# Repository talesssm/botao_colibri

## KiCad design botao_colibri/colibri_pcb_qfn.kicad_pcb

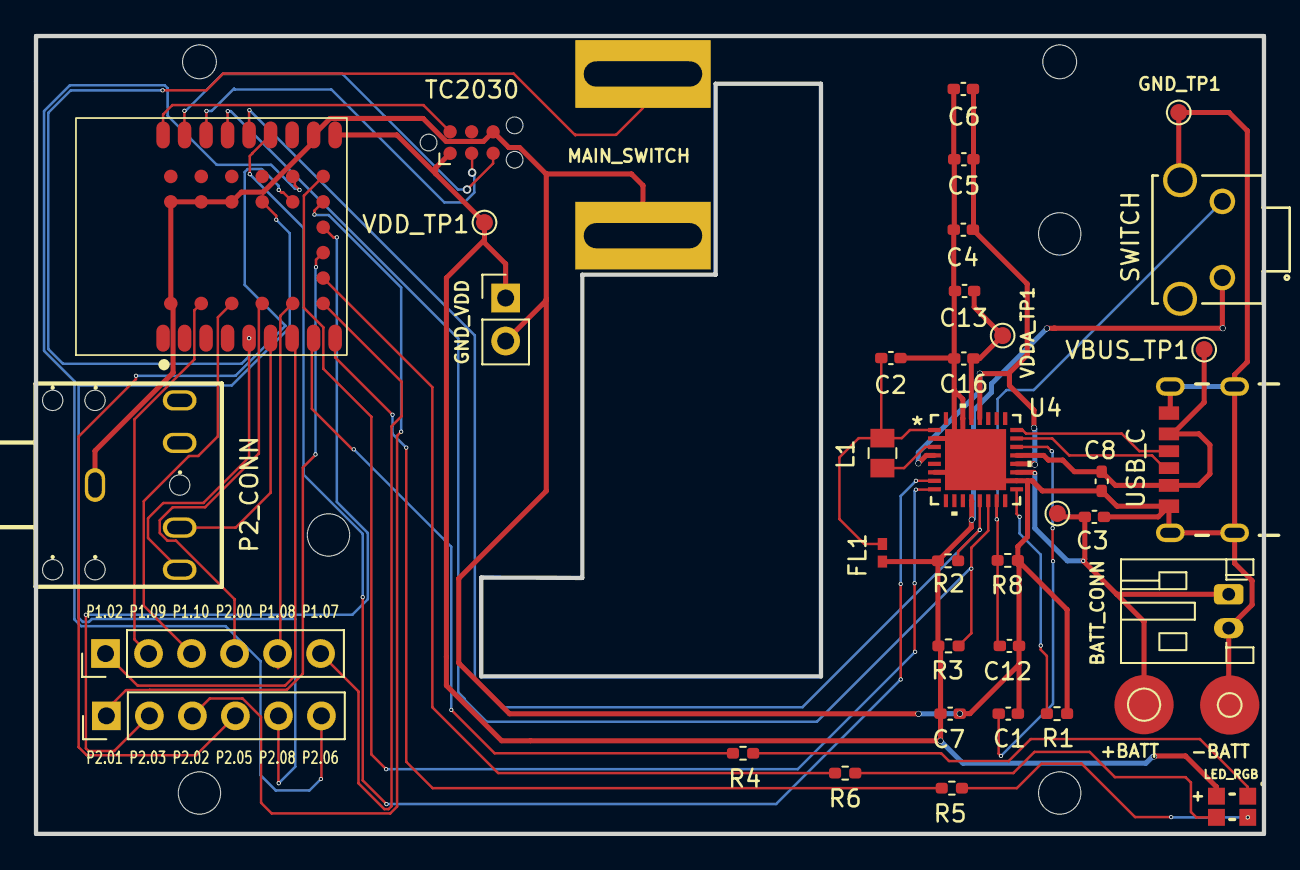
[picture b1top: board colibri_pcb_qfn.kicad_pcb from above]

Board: 2 copper layers, 72.5 x 47.1 mm, 45 parts (0 on the bottom side), 40 nets.

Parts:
+BATT: Conn_01x02; TestPoint_Pad_D1.5mm
-BATT: TestPoint; TestPoint_Pad_D1.0mm
BATT_CONN: Conn_01x02; JST_PH_S2B-PH-K_1x02_P2.00mm_Horizontal
C1, C3, C4, C5, C6, C7, C8: C_Small; C_0402_1005Metric_Pad0.74x0.62mm_HandSolder
C2: 10µF; C_0402_1005Metric_Pad0.74x0.62mm_HandSolder
C12, C13: 100nF; C_0402_1005Metric_Pad0.74x0.62mm_HandSolder
C16: 1uF; C_0402_1005Metric_Pad0.74x0.62mm_HandSolder
FL1: BLM15AG121SN1D; IND_BLM15_0402_MUR
GND_TP1: TestPoint; TestPoint_Pad_D1.0mm
GND_VDD: Conn_01x02; PinHeader_1x02_P2.54mm_Vertical
H1, H2, H3, H4, H5, H6: NPTH
L1: 2.2µH; LQM21PN2R2MGRD
LED_RGB: WL-SFCD_0805
MAIN_SWITCH: SW_Push; sw_principal
P1.02 P1.09 P1.10 P2.00 P1.08 P1.07, P2.01 P2.03 P2.02 P2.05 P2.08 P2.06: Conn_01x06; PinHeader_1x06_P2.54mm_Vertical
P2_CONN: PJ-307C; AUDIO-TH_PJ307C
R1: 360kR; R_0402_1005Metric_Pad0.72x0.64mm_HandSolder
R2, R3: 4.7kR; R_0402_1005Metric_Pad0.72x0.64mm_HandSolder
R4, R5, R6: R_Small; R_0402_1005Metric_Pad0.72x0.64mm_HandSolder
R8: 330kR; R_0402_1005Metric_Pad0.72x0.64mm_HandSolder
SWITCH: B3F-3122
TC2030: TC2030; Tag-Connect_TC2030-IDC-NL_2x03_P1.27mm_Vertical
U1: ME54BS12; ME54BS12_V1.0
U4: NPM1300-QEAA-R7; NPM1300_QFN32_5X5_NOR
USB_C: USB4970-00-A_REVA; GCT_USB4970-00-A_REVA
VBATT_TP1: TestPoint; TestPoint_Pad_D1.0mm
VBUS_TP1: TestPoint; TestPoint_Pad_D1.0mm
VDDA_TP1: TestPoint; TestPoint_Pad_D1.0mm
VDD_TP1: TestPoint; TestPoint_Pad_D1.0mm

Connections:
+BATT: +BATT.1 (Pin_1_1), BATT_CONN.1, C3.1, U4.19 (VBAT), VBATT_TP1.1 (1_1)
BTN_PWR: C12.1, R8.2, SWITCH.2, U4.15 (SHPHLD)
GND: -BATT.1 (1_1), BATT_CONN.2, C1.2, C2.2, C3.2, C4.2, C5.2, C6.2, C7.2, C8.2, C12.2, C13.2, C16.2, GND_TP1.1 (1_1), GND_VDD.2, MAIN_SWITCH.2, P2_CONN.1, R1.1, R8.1, SWITCH.4, TC2030.6, U1.11 (GND), U1.A1 (GND), U1.A5 (GND), U1.B5 (GND), U1.C5 (GND), U4.2 (PVSS1), U4.6 (PVSS2), U4.18 (NTC), U4.30 (LSIN2/VINLDO2), U4.31 (LSOUT2/VOUTLDO2), U4.33 (AVSS), USB_C.A12 (GND), USB_C.B12 (GND), USB_C.SH1 (SHELL_GND), USB_C.SH2 (SHELL_GND), USB_C.SH3 (SHELL_GND), USB_C.SH4 (SHELL_GND)
I2C_SCL: R3.1, U1.15 (P0.03), U4.14 (SCL)
I2C_SDA: R2.1, U1.14 (P0.02), U4.13 (SDA)
LED_B: R6.2, U1.F2 (P1.04/AIN0)
LED_G: R5.2, U1.9 (P1.05/AIN1)
LED_R: R4.1, U1.8 (P1.06/AIN2)
NPM1300_EN: U1.F6 (P2.04), U4.8 (GPIO1)
NPM1300_INT: U1.13 (P0.01), U4.7 (GPIO0)
NRESET: TC2030.2, U1.18 (~NRESET)
unnamed: LED_RGB.1, R4.2
unnamed: LED_RGB.2, R5.1
unnamed: LED_RGB.3, R6.1
unnamed: L1.2, U4.3 (SW1)
unnamed: C1.1, U4.22 (VBUSOUT)
unnamed: C2.1, FL1.1, L1.1, U4.1 (VOUT1)
unnamed: R1.2, U4.17 (VSET1)
P1.02: P1.02 P1.09 P1.10 P2.00 P1.08 P1.07.1, U1.7 (P1.02/NFC1)
P1.07: P1.02 P1.09 P1.10 P2.00 P1.08 P1.07.6, U1.F1 (P1.07/AIN3)
P1.08: P1.02 P1.09 P1.10 P2.00 P1.08 P1.07.5, U1.E1 (P1.08)
P1.09: P1.02 P1.09 P1.10 P2.00 P1.08 P1.07.2, U1.B1 (P1.09)
P1.10: P1.02 P1.09 P1.10 P2.00 P1.08 P1.07.3, U1.C1 (P1.10)
P2.00: P1.02 P1.09 P1.10 P2.00 P1.08 P1.07.4, U1.D1 (P2.00)
P2.01: P2.01 P2.03 P2.02 P2.05 P2.08 P2.06.1, U1.F3 (P2.01)
P2.02: P2.01 P2.03 P2.02 P2.05 P2.08 P2.06.3, U1.F5 (P2.02)
P2.03: P2.01 P2.03 P2.02 P2.05 P2.08 P2.06.2, U1.F4 (P2.03)
P2.05: P2.01 P2.03 P2.02 P2.05 P2.08 P2.06.4, U1.E5 (P2.05)
P2.06: P2.01 P2.03 P2.02 P2.05 P2.08 P2.06.6, U1.E6 (P2.06)
P2.08: P2.01 P2.03 P2.02 P2.05 P2.08 P2.06.5, U1.D5 (P2.08)
P2_SENSE: P2_CONN.4, U1.6 (P1.03/NFC2)
P2_SQUARE_WAVE: MAIN_SWITCH.1, P2_CONN.5, U1.5 (P1.14/AIN7)
PVDD: C4.1, C5.1, C6.1, U4.4 (PVDD), U4.20 (VSYS), U4.28 (LSIN1/VINLDO1)
SWCLK: TC2030.5, U1.17 (SWDCLK)
SWDIO: TC2030.3, U1.16 (SWDIO)
USB.CC1: U4.23 (CC1), USB_C.A5 (CC1)
USB.CC2: U4.24 (CC2), USB_C.B5 (CC2)
USB.VBUS: C8.1, U4.21 (VBUS), USB_C.A9 (VBUS), USB_C.B9 (VBUS), VBUS_TP1.1 (1_1)
VDD: C7.1, FL1.2, GND_VDD.1, LED_RGB.4, R2.2, R3.2, SWITCH.1, TC2030.1, U1.10 (VCC), U4.12 (VDDIO), VDD_TP1.1 (1_1)
VDDA: C13.1, C16.1, U4.29 (LSOUT1/VOUTLDO1), VDDA_TP1.1 (1_1)

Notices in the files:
parts and their libraries:
Copyright 2016 Accelerated Designs. All rights reserved.
